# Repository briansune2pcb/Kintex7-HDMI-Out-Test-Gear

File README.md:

# Kintex7-HDMI-Out-Test-Gear

An Test PCB for Kintex 7 FPGA board under Eagle CAD.

An additional KiCAD PCB is also provided.

## T11

```
set_property IOSTANDARD TMDS_33 [get_ports {hdmi_clk[1]}]
set_property IOSTANDARD TMDS_33 [get_ports {hdmi_clk[0]}]
set_property IOSTANDARD TMDS_33 [get_ports {hdmi_d0[1]}]
set_property IOSTANDARD TMDS_33 [get_ports {hdmi_d0[0]}]
set_property IOSTANDARD TMDS_33 [get_ports {hdmi_d1[1]}]
set_property IOSTANDARD TMDS_33 [get_ports {hdmi_d1[0]}]
set_property IOSTANDARD TMDS_33 [get_ports {hdmi_d2[0]}]
set_property IOSTANDARD TMDS_33 [get_ports {hdmi_d2[1]}]

set_property PACKAGE_PIN AG29  [get_ports {hdmi_clk[1]}]
set_property PACKAGE_PIN AC29 [get_ports {hdmi_d0[1]}]
set_property PACKAGE_PIN AB29 [get_ports {hdmi_d1[1]}]
set_property PACKAGE_PIN Y30 [get_ports {hdmi_d2[1]}]
```

## T10

```
set_property IOSTANDARD TMDS_33 [get_ports {hdmi_clk[1]}]
set_property IOSTANDARD TMDS_33 [get_ports {hdmi_clk[0]}]
set_property IOSTANDARD TMDS_33 [get_ports {hdmi_d0[1]}]
set_property IOSTANDARD TMDS_33 [get_ports {hdmi_d0[0]}]
set_property IOSTANDARD TMDS_33 [get_ports {hdmi_d1[1]}]
set_property IOSTANDARD TMDS_33 [get_ports {hdmi_d1[0]}]
set_property IOSTANDARD TMDS_33 [get_ports {hdmi_d2[0]}]
set_property IOSTANDARD TMDS_33 [get_ports {hdmi_d2[1]}]

set_property PACKAGE_PIN F20 [get_ports {hdmi_d0[1]}]
set_property PACKAGE_PIN D17 [get_ports {hdmi_d2[1]}]
set_property PACKAGE_PIN E19 [get_ports {hdmi_d1[1]}]
set_property PACKAGE_PIN C20 [get_ports {hdmi_clk[1]}]
```

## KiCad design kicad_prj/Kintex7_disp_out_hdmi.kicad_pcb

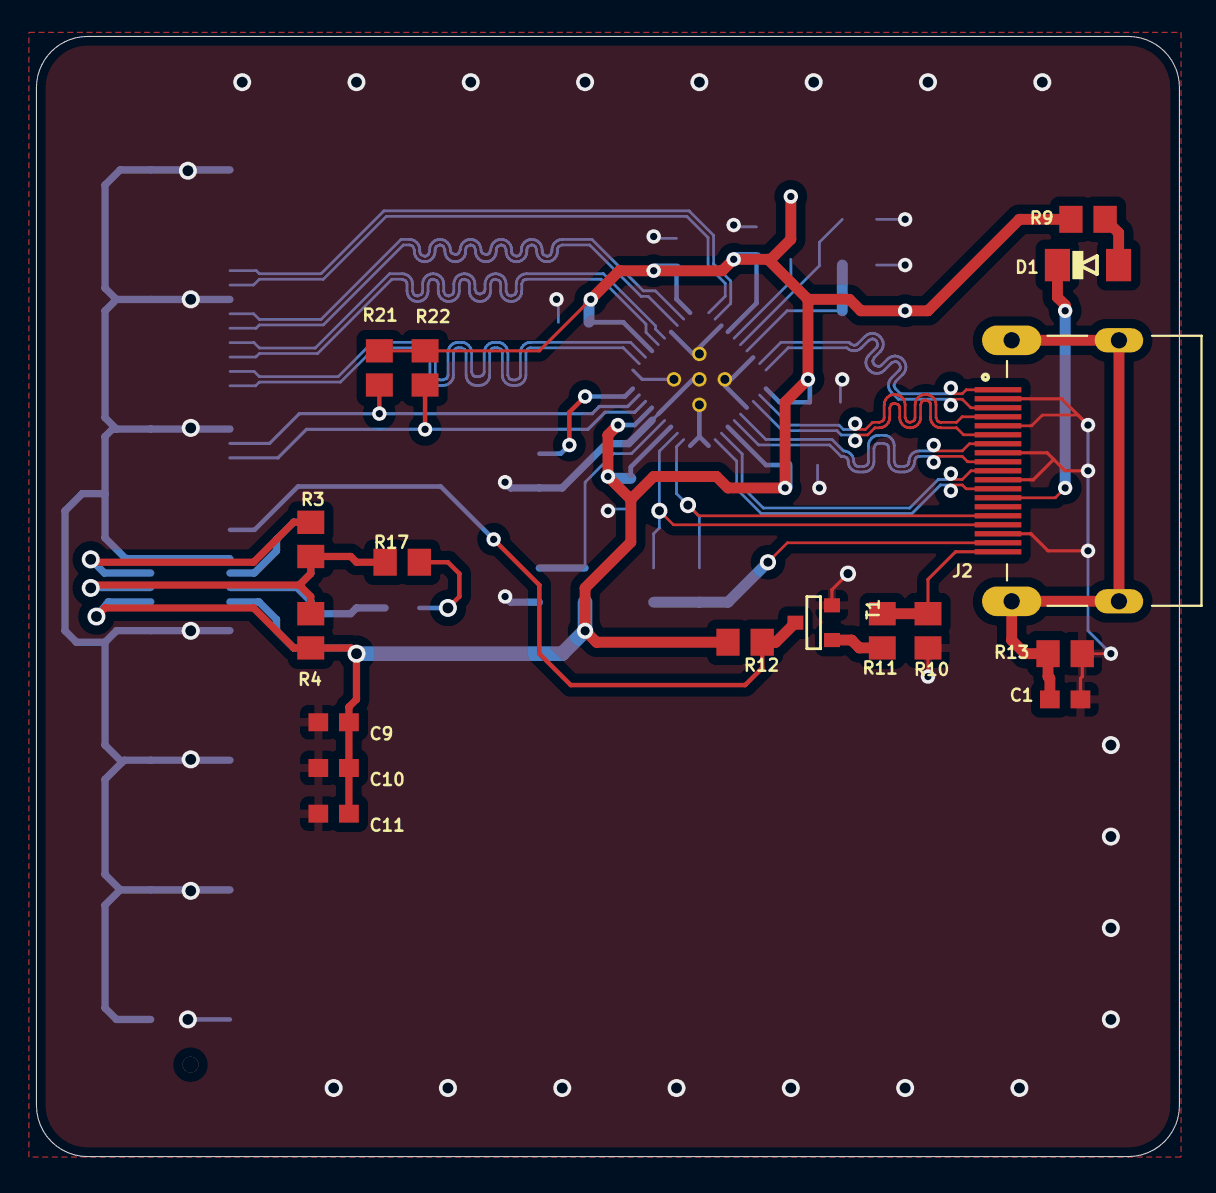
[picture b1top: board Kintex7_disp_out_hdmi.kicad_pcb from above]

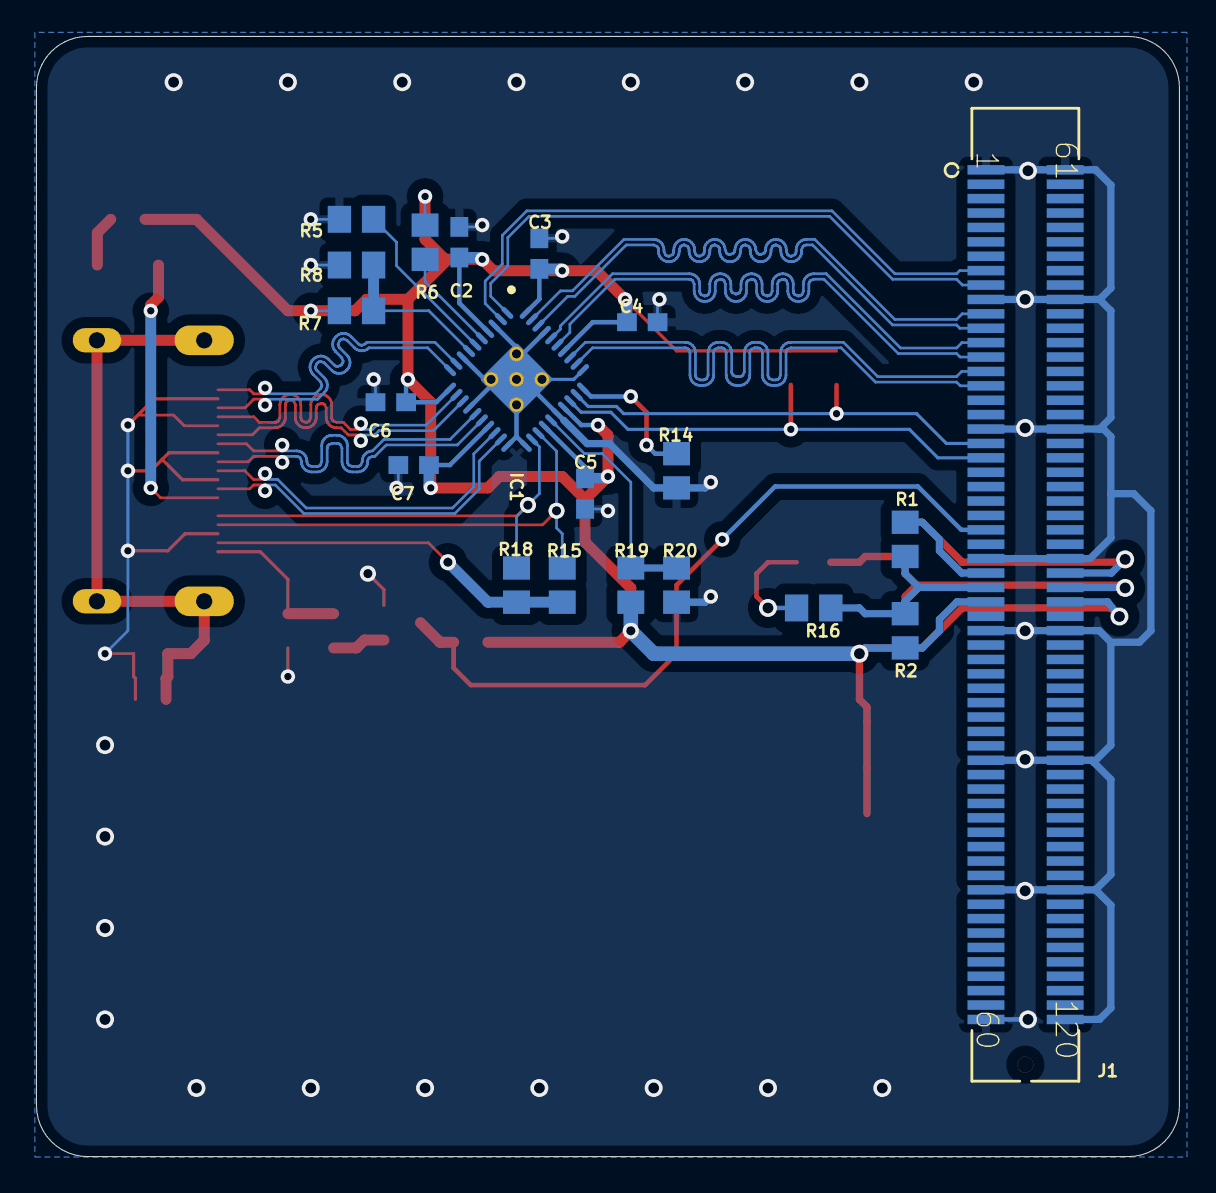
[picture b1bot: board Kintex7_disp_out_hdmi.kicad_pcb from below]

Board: 2 copper layers, 63.5 x 62.2 mm, 37 parts (20 on the bottom side), 39 nets.

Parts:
C1, C2, C3, C4, C5, C6, C7, C9, C10, C11: C0603
D1: MINIMELF
IC1: TMDS141RHAR; QFN50P600X600X100-41N
J1: 5177985-5; CONN_5177985-5
J2: 1827059-3; TE_1827059-3
R1, R2, R3, R4, R16, R17: R0805
R5, R6, R7, R8, R10, R11, R13, R15, R18, R19, R20, R21, R22: 10k; R0805
R9: 27k; R0805
R12, R14: 4k7; R0805
T1: SOT-23

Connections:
+3V3: C2.1, C3.1, C4.1, C5.1, C6.1, C7.1, C9.1, C10.1, C11.1, IC1.4, IC1.11, IC1.17, IC1.24, IC1.27, IC1.34, IC1.40, J1.31, J1.91, R2.2, R4.2, R6.1, R7.2, R9.2, R12.1, R19.1, R21.1, R22.1
CAM_DOVDD18: R16.2, R17.2
GND: C1.1, C2.2, C3.2, C4.2, C5.2, C6.2, C7.2, C9.2, C10.2, C11.2, IC1.3, IC1.8, IC1.14, IC1.20, IC1.21, IC1.26, IC1.31, IC1.37, IC1.41, IC1.P$1, IC1.P$2, IC1.P$3, IC1.P$4, IC1.P$5, J1.1, J1.10, J1.19, J1.28, J1.33, J1.42, J1.51, J1.60, J1.61, J1.70, J1.79, J1.88, J1.93, J1.102, J1.111, J1.120, J2.2, J2.5, J2.8, J2.11, J2.17, R5.1, R8.1, R10.1, R13.2, R14.2, R20.2, T1.2
HDMI_HPD: J1.26, R12.2, T1.1
HDMI_TX_5V: J2.18, R15.2, R18.2
unnamed: D1.A, R9.1
unnamed: J1.90, R3.1, R4.1, R17.1
unnamed: J1.29, R1.2
unnamed: J1.89, R3.2
unnamed: IC1.6, R5.2
unnamed: IC1.5, R6.2
unnamed: D1.C, J2.13
unnamed: J1.30, R1.1, R2.1, R16.1
unnamed: IC1.25, R19.2, R20.1
unnamed: R11.2, T1.3
unnamed: C1.2, J2.S1, J2.S2, J2.S3, J2.S4, R13.1
unnamed: IC1.30, R14.1
unnamed: J2.19, R10.2, R11.1
PRE: IC1.7, R7.1, R8.2
RX0_N: IC1.35, J1.14
RX0_P: IC1.36, J1.13
RX1_N: IC1.38, J1.12
RX1_P: IC1.39, J1.11
RX2_N: IC1.1, J1.9
RX2_P: IC1.2, J1.8
RXC_N: IC1.32, J1.16
RXC_P: IC1.33, J1.15
RX_SCL: IC1.29, J1.20, R21.2
RX_SDA: IC1.28, J1.21, R22.2
TX0_N: IC1.16, J2.9
TX0_P: IC1.15, J2.7
TX1_N: IC1.13, J2.6
TX1_P: IC1.12, J2.4
TX2_N: IC1.10, J2.3
TX2_P: IC1.9, J2.1
TXC_N: IC1.19, J2.12
TXC_P: IC1.18, J2.10
TX_SCL: IC1.22, J2.15, R18.1
TX_SDA: IC1.23, J2.16, R15.1
